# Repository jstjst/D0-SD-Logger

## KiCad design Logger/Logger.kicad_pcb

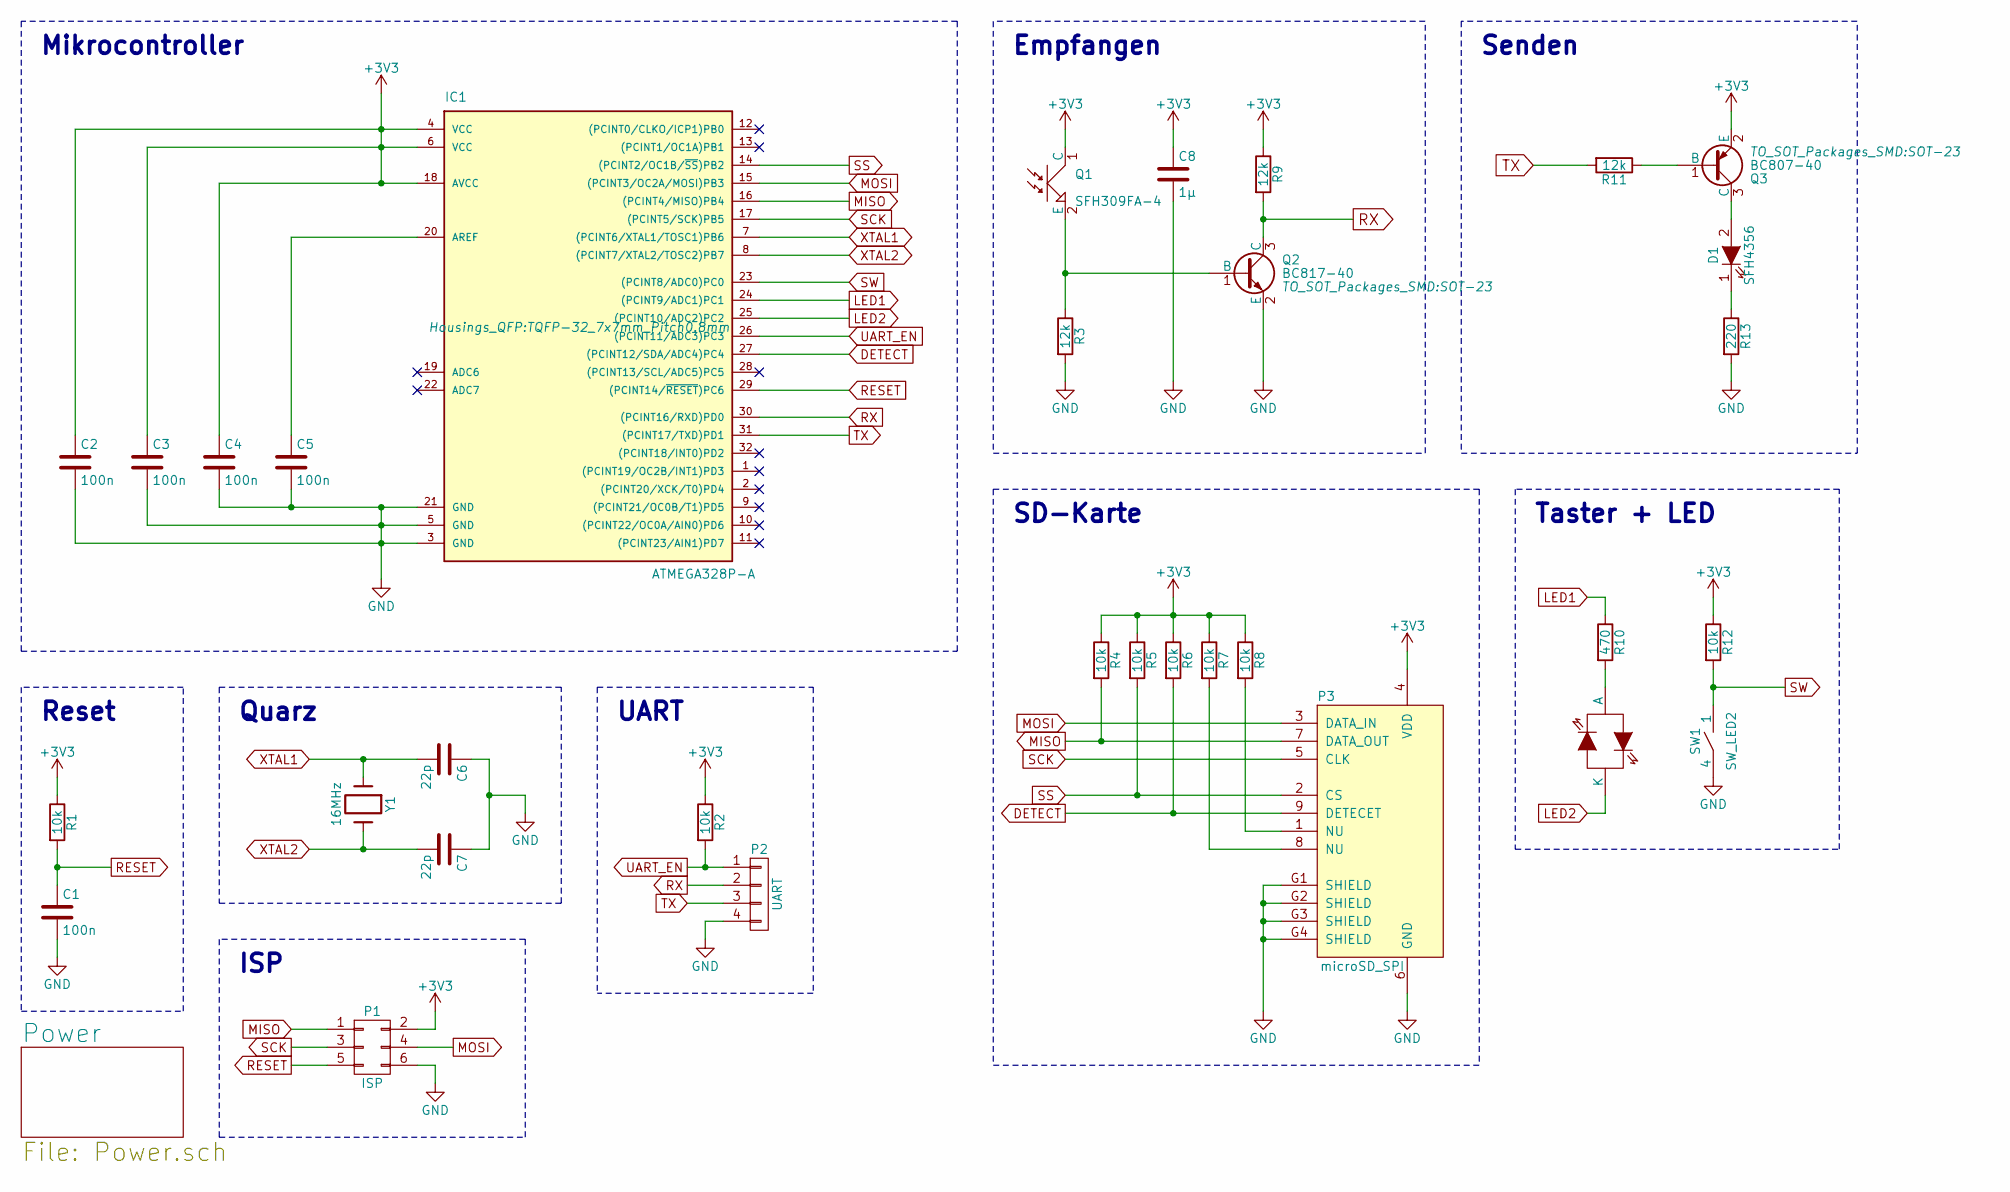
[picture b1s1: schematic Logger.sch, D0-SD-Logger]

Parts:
C1, C2, C3, C4, C5: 100n; C_0603_HandSoldering
C6, C7: 22p; C_0603_HandSoldering
C8: 1µ; C_0603_HandSoldering
D1: SFH4356; LED-3MM-SMD
IC1: ATMEGA328P-A; TQFP-32_7x7mm_Pitch0.8mm
P1: ISP; Pin_Header_Straight_2x03_Pitch2.54mm
P2: UART; Pin_Header_Straight_1x04_Pitch2.54mm
P3: microSD_SPI; 105162-0101
Q1: SFH309FA-4; LED-3MM-SMD
Q2: BC817-40; SOT-23
Q3: BC807-40; SOT-23
R1, R2, R4, R5, R6, R7, R8, R12: 10k; R_0603_HandSoldering
R3, R9, R11: 12k; R_0603_HandSoldering
R10: 470; R_0603_HandSoldering
R13: 220; R_0603_HandSoldering
SW1: SW_LED2; 4FSH9XX
Y1: 16MHz; SMD_7x4

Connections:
+3V3: C2.1, C3.1, C4.1, C8.1, IC1.4 (VCC), IC1.6 (VCC), IC1.18 (AVCC), P1.2, P3.4 (VDD), Q1.1 (C), Q3.2 (E), R1.1, R2.1, R4.1, R5.1, R6.1, R7.1, R8.1, R9.1, R12.1; also elsewhere on the board
DETECT: IC1.27 ((PCINT12/SDA/ADC4)PC4), P3.9 (DETECET), R6.2
GND: C1.2, C2.2, C3.2, C4.2, C5.2, C6.1, C7.1, C8.2, IC1.3 (GND), IC1.5 (GND), IC1.21 (GND), P1.6, P2.4, P3.6 (GND), P3.G1 (SHIELD), P3.G2 (SHIELD), P3.G3 (SHIELD), P3.G4 (SHIELD), Q2.2 (E), R3.2, R13.2, SW1.4; also elsewhere on the board
LED1: IC1.24 ((PCINT9/ADC1)PC1), R10.1
LED2: IC1.25 ((PCINT10/ADC2)PC2), SW1.2 (K)
MISO: IC1.16 ((PCINT4/MISO)PB4), P1.1, P3.7 (DATA_OUT), R4.2
MOSI: IC1.15 ((PCINT3/OC2A/MOSI)PB3), P1.4, P3.3 (DATA_IN)
unnamed: C5.1, IC1.20 (AREF)
unnamed: D1.1 (K), R13.1
unnamed: D1.2 (A), Q3.3 (C)
unnamed: P3.1 (NU), R8.2
unnamed: P3.8 (NU), R7.2
unnamed: Q1.2 (E), Q2.1 (B), R3.1
unnamed: Q3.1 (B), R11.1
unnamed: R10.2, SW1.3 (A)
RESET: C1.1, IC1.29 ((PCINT14/~RESET~)PC6), P1.5, R1.2
RX: IC1.30 ((PCINT16/RXD)PD0), P2.2, Q2.3 (C), R9.2
SCK: IC1.17 ((PCINT5/SCK)PB5), P1.3, P3.5 (CLK)
SS: IC1.14 ((PCINT2/OC1B/~SS~)PB2), P3.2 (CS), R5.2
SW: IC1.23 ((PCINT8/ADC0)PC0), R12.2, SW1.1
TX: IC1.31 ((PCINT17/TXD)PD1), P2.3, R11.2
UART_EN: IC1.26 ((PCINT11/ADC3)PC3), P2.1, R2.2
XTAL1: C6.2, IC1.7 ((PCINT6/XTAL1/TOSC1)PB6), Y1.1
XTAL2: C7.2, IC1.8 ((PCINT7/XTAL2/TOSC2)PB7), Y1.2

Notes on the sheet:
Empfangen
Senden
SD-Karte
ISP
Quarz
Reset
UART
Mikrocontroller
Taster + LED

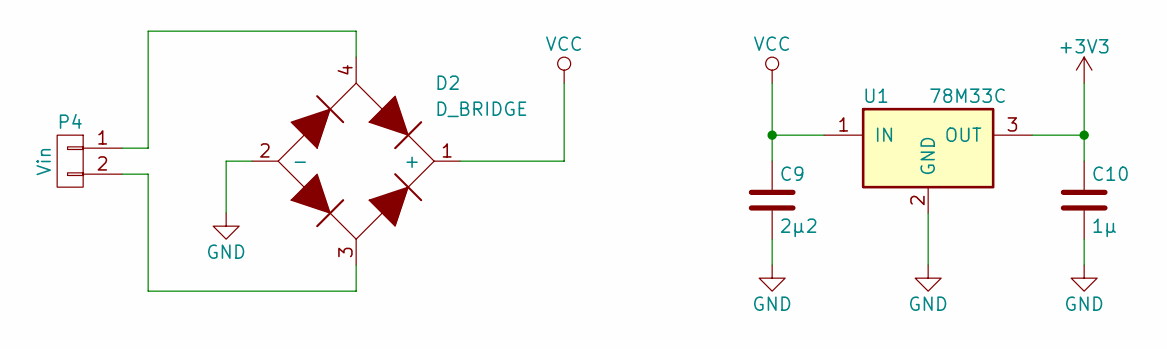
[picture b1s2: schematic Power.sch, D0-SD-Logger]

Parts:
C9: 2µ2; C_0603_HandSoldering
C10: 1µ; C_0603_HandSoldering
D2: D_BRIDGE; SOIC-4
P4: Vin; Pin_Header_Straight_1x02_Pitch2.54mm
U1: 78M33C; TO-252-2Lead

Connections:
+3V3: C10.1, U1.3 (OUT); also elsewhere on the board
GND: C9.2, C10.2, D2.2 (-), U1.2 (GND); also elsewhere on the board
unnamed: D2.3, P4.2
unnamed: D2.4, P4.1
VCC: C9.1, D2.1 (+), U1.1 (IN)

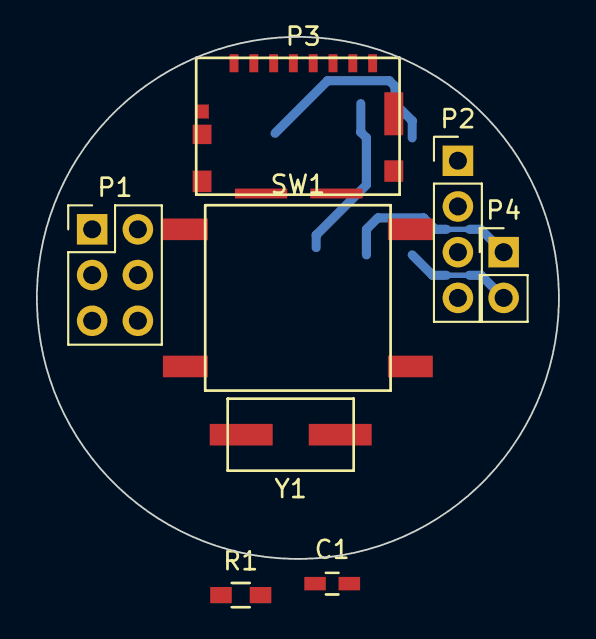
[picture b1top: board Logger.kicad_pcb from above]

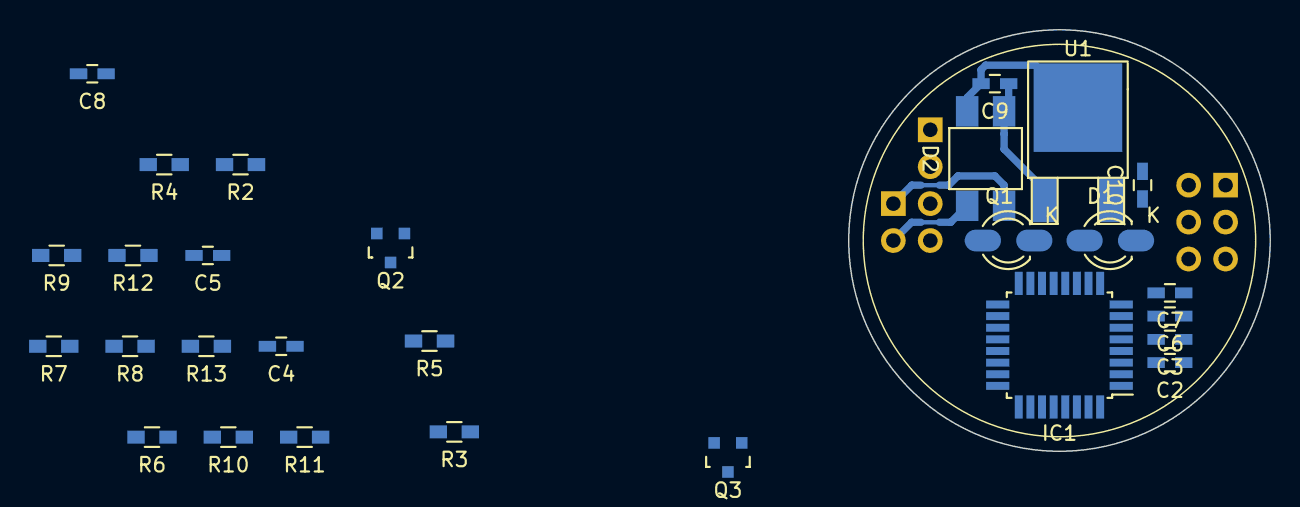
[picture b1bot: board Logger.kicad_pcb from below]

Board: 2 copper layers, 29.0 x 29.0 mm, 36 parts (28 on the bottom side), 27 nets.

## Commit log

2017-12-02 Dumps
2017-12-07 schematic with Mega328
2017-12-23 Schaltplan...
2017-12-23 Schaltplan Rev A
2017-12-23 Schaltplan Rev B
2018-01-07 removed some Kicad files
2018-01-07 Schaltplan Rev C and BOM file
2018-01-19 SOIC-4 3D model
2018-01-19 Schaltplan Rev D, Gleichrichter geaendert
2018-01-19 PCB save
2018-01-21 switch datasheet
2018-01-21 switch 3d model
2018-01-21 quarz 3d model
